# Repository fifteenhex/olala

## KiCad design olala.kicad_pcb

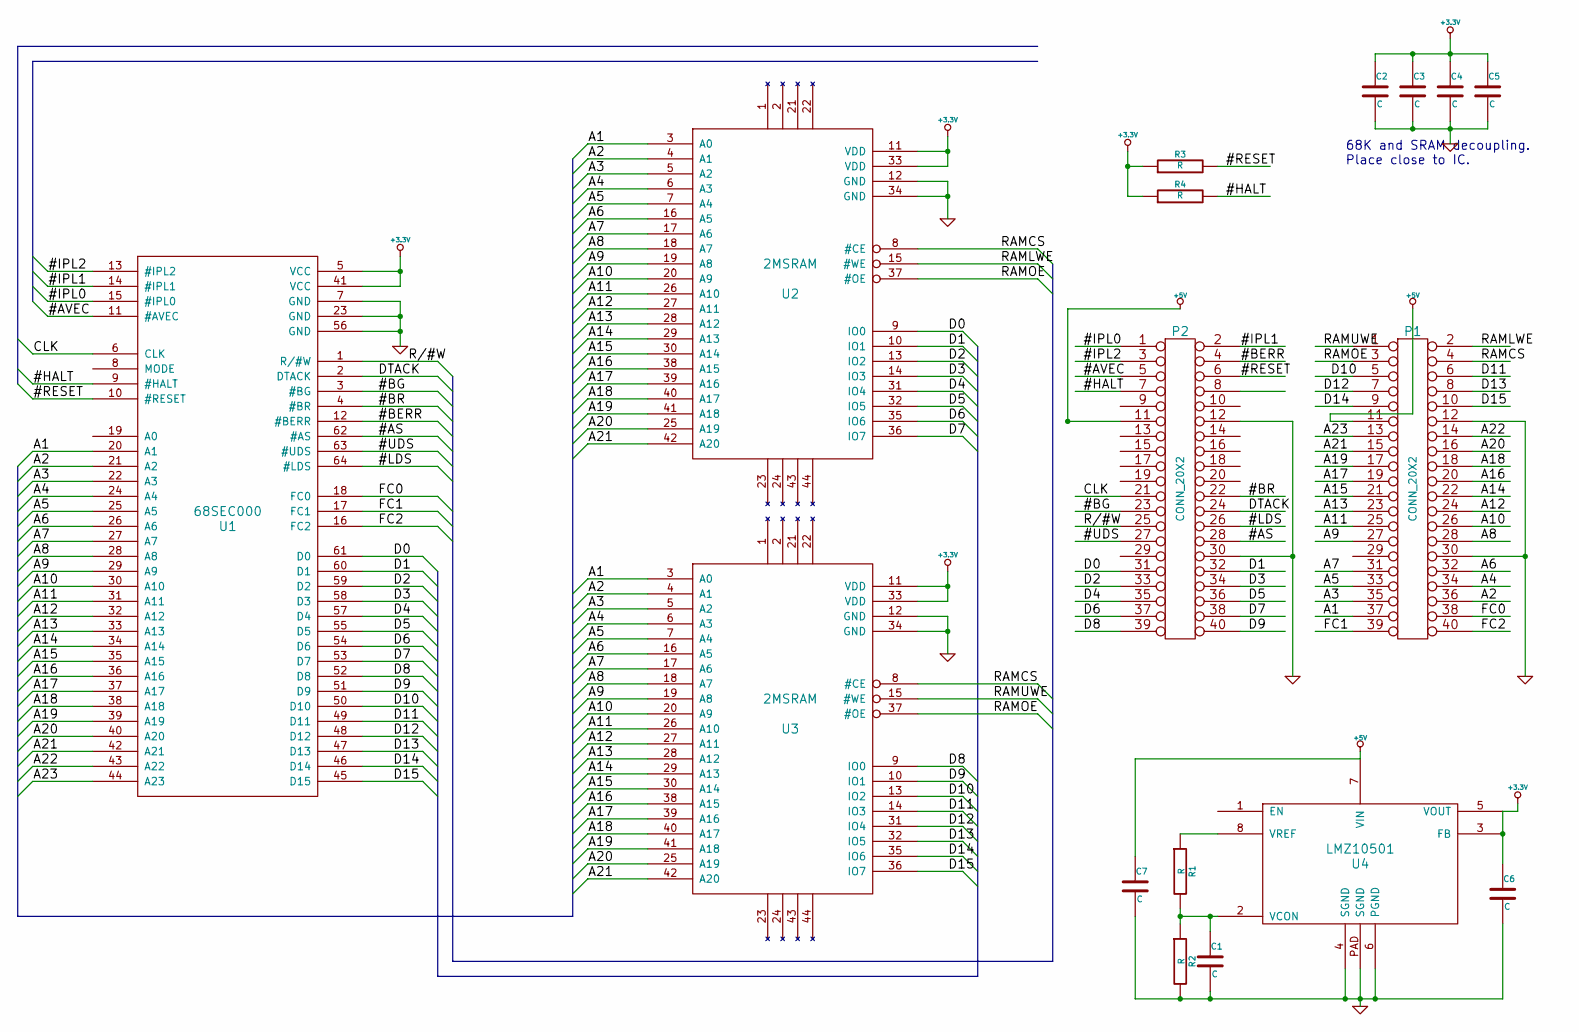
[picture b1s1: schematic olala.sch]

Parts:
C1, C2, C3, C4, C5, C6, C7: C
P1, P2: CONN_20X2
R1, R2, R3, R4: R
U1: 68SEC000
U2, U3: 2MSRAM
U4: LMZ10501

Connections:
+3.3V: C2.1, C3.1, C4.1, C5.1, C6.1, R3.1, R4.1, U1.5 (VCC), U1.41 (VCC), U2.11 (VDD), U2.33 (VDD), U3.11 (VDD), U3.33 (VDD), U4.3 (FB), U4.5 (VOUT)
+5V: C7.1, P1.11, P2.11, U4.7 (VIN)
/#AS: P2.28, U1.62 (#AS)
/#AVEC: P2.5, U1.11 (#AVEC)
/#BERR: P2.4, U1.12 (#BERR)
/#BG: P2.23, U1.3 (#BG)
/#BR: P2.22, U1.4 (#BR)
/#HALT: P2.7, R4.2, U1.9 (#HALT)
/#IPL0: P2.1, U1.15 (#IPL0)
/#IPL1: P2.2, U1.14 (#IPL1)
/#IPL2: P2.3, U1.13 (#IPL2)
/#LDS: P2.26, U1.64 (#LDS)
/#RESET: P2.6, R3.2, U1.10 (#RESET)
/#UDS: P2.27, U1.63 (#UDS)
/A1: P1.37, U1.20 (A1), U2.3 (A0), U3.3 (A0)
/A2: P1.36, U1.21 (A2), U2.4 (A1), U3.4 (A1)
/A3: P1.35, U1.22 (A3), U2.5 (A2), U3.5 (A2)
/A4: P1.34, U1.24 (A4), U2.6 (A3), U3.6 (A3)
/A5: P1.33, U1.25 (A5), U2.7 (A4), U3.7 (A4)
/A6: P1.32, U1.26 (A6), U2.16 (A5), U3.16 (A5)
/A7: P1.31, U1.27 (A7), U2.17 (A6), U3.17 (A6)
/A8: P1.28, U1.28 (A8), U2.18 (A7), U3.18 (A7)
/A9: P1.27, U1.29 (A9), U2.19 (A8), U3.19 (A8)
/A10: P1.26, U1.30 (A10), U2.20 (A9), U3.20 (A9)
/A11: P1.25, U1.31 (A11), U2.26 (A10), U3.26 (A10)
/A12: P1.24, U1.32 (A12), U2.27 (A11), U3.27 (A11)
/A13: P1.23, U1.33 (A13), U2.28 (A12), U3.28 (A12)
/A14: P1.22, U1.34 (A14), U2.29 (A13), U3.29 (A13)
/A15: P1.21, U1.35 (A15), U2.30 (A14), U3.30 (A14)
/A16: P1.20, U1.36 (A16), U2.38 (A15), U3.38 (A15)
/A17: P1.19, U1.37 (A17), U2.39 (A16), U3.39 (A16)
/A18: P1.18, U1.38 (A18), U2.40 (A17), U3.40 (A17)
/A19: P1.17, U1.39 (A19), U2.41 (A18), U3.41 (A18)
/A20: P1.16, U1.40 (A20), U2.25 (A19), U3.25 (A19)
/A21: P1.15, U1.42 (A21), U2.42 (A20), U3.42 (A20)
/A22: P1.14, U1.43 (A22)
/A23: P1.13, U1.44 (A23)
/CLK: P2.21, U1.6 (CLK)
/D0: P2.31, U1.61 (D0), U2.9 (IO0)
/D1: P2.32, U1.60 (D1), U2.10 (IO1)
/D2: P2.33, U1.59 (D2), U2.13 (IO2)
/D3: P2.34, U1.58 (D3), U2.14 (IO3)
/D4: P2.35, U1.57 (D4), U2.31 (IO4)
/D5: P2.36, U1.55 (D5), U2.32 (IO5)
/D6: P2.37, U1.54 (D6), U2.35 (IO6)
/D7: P2.38, U1.53 (D7), U2.36 (IO7)
/D8: P2.39, U1.52 (D8), U3.9 (IO0)
/D9: P2.40, U1.51 (D9), U3.10 (IO1)
/D10: P1.5, U1.50 (D10), U3.13 (IO2)
/D11: P1.6, U1.49 (D11), U3.14 (IO3)
/D12: P1.7, U1.48 (D12), U3.31 (IO4)
/D13: P1.8, U1.47 (D13), U3.32 (IO5)
/D14: P1.9, U1.46 (D14), U3.35 (IO6)
/D15: P1.10, U1.45 (D15), U3.36 (IO7)
/DTACK: P2.24, U1.2 (DTACK)
/FC0: P1.38, U1.18 (FC0)
/FC1: P1.39, U1.17 (FC1)
/FC2: P1.40, U1.16 (FC2)
/R/#W: P2.25, U1.1 (R/#W)
/RAMCS: P1.4, U2.8 (#CE), U3.8 (#CE)
/RAMLWE: P1.2, U2.15 (#WE)
/RAMOE: P1.3, U2.37 (#OE), U3.37 (#OE)
/RAMUWE: P1.1, U3.15 (#WE)
GND: C1.2, C2.2, C3.2, C4.2, C5.2, C6.2, C7.2, P1.12, P1.30, P2.12, P2.30, R2.2, U1.7 (GND), U1.23 (GND), U1.56 (GND), U2.12 (GND), U2.34 (GND), U3.12 (GND), U3.34 (GND), U4.4 (SGND), U4.6 (PGND), U4.PAD (SGND)
unnamed: R1.1, U4.8 (VREF)
unnamed: C1.1, R1.2, R2.1, U4.2 (VCON)

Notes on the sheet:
68K and SRAM decoupling. Place close to IC.

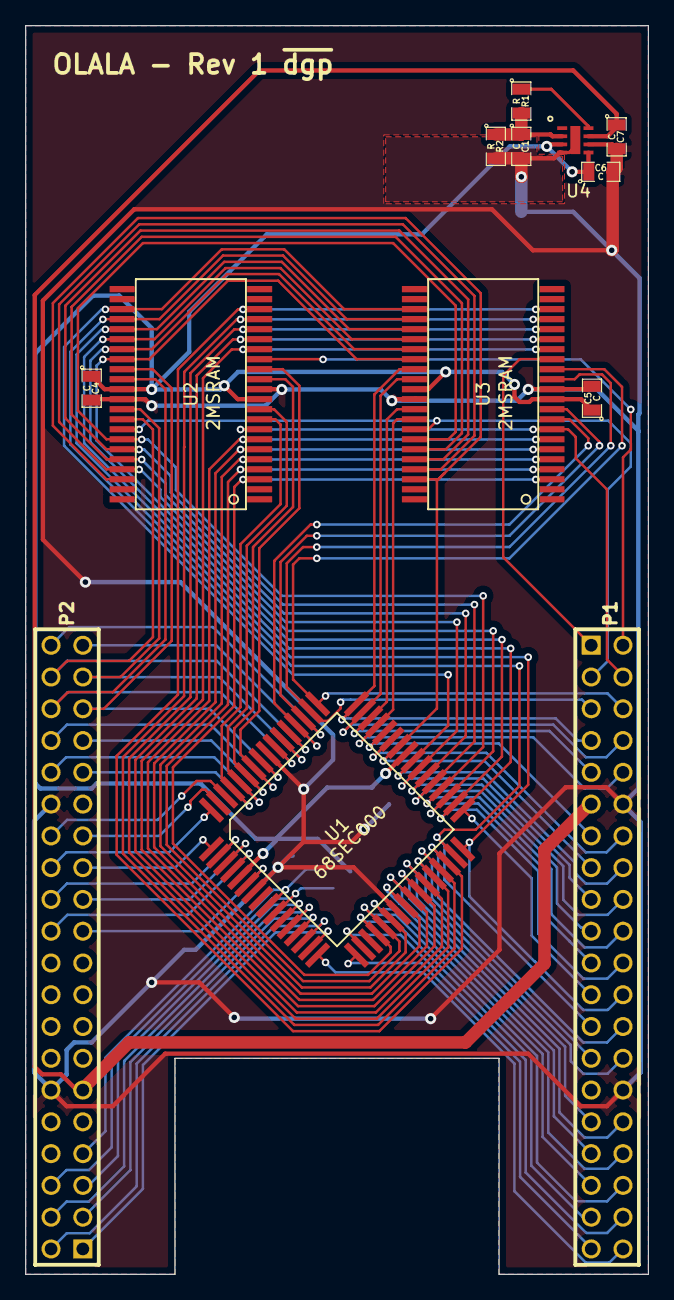
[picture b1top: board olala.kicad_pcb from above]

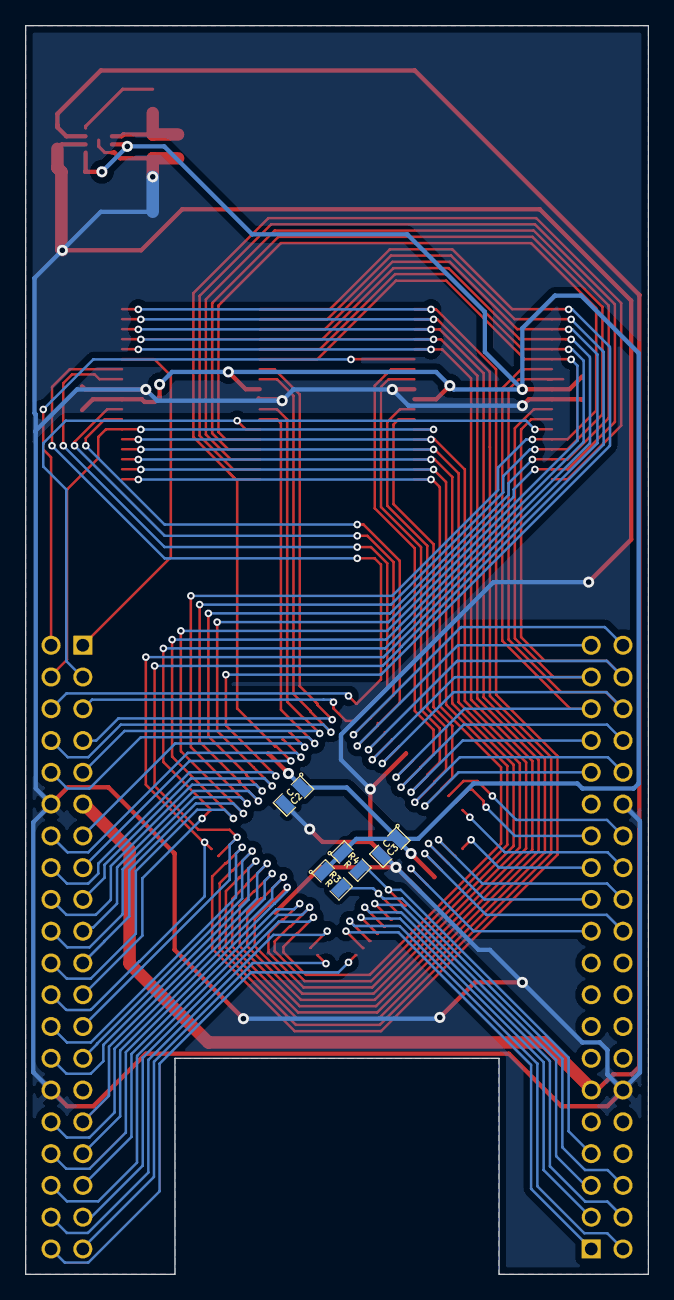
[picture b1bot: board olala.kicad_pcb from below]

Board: 2 copper layers, 49.8 x 99.8 mm, 17 parts (4 on the bottom side), 66 nets.

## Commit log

2017-06-28 All of it. Loads of crap too.
